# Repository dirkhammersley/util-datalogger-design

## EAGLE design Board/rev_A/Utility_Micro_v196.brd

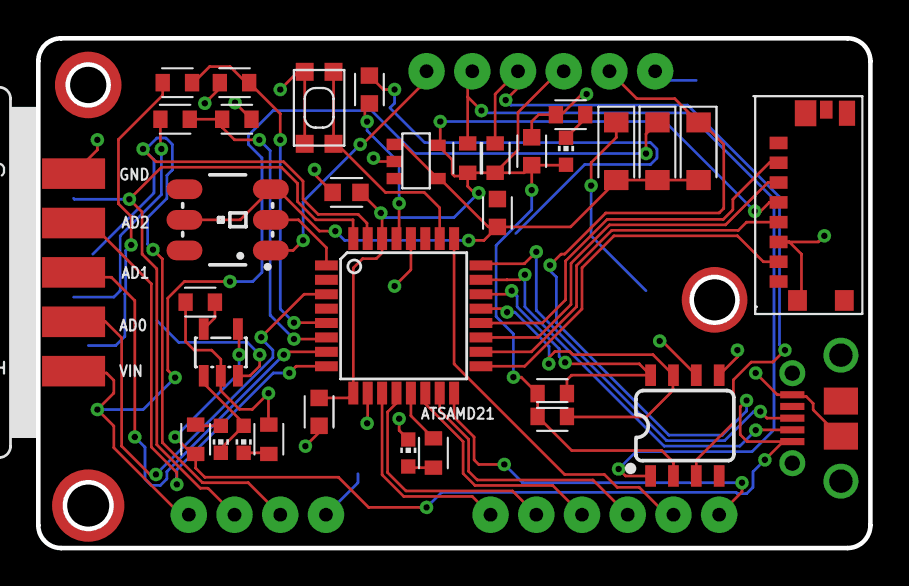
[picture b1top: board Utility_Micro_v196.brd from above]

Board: 2 copper layers, 46.2 x 28.3 mm, 38 parts (1 on the bottom side), 43 nets.

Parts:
ATSAMD21: ATSAMD21TQFP; TQFP32-08
C1, C2: 100nF; CAPC1608X85
C5, C8: C_CHIP-0603(1608-METRIC); CAPC1608X85
C7: 1uF; CAPC1608X85
D1, D2, D3: SCHOTTKY_MBR0520LT1GDO-219-AB(SOD123F); SODFL3718X115
IC1: MCP73831/OT; SOT23-5L
LED1, LED2, LED3, LED8: CHIP-LED0603
LIR_2450: LIR2450H; BC-2005
R1, R6, R7: 470; RESC1608X60
R2, R4: 100; RESC1608X60
R3: 2.2k; RESC1608X60
R5: 12k; RESC1608X60
R8, R9, R12, R13: 10k; RESC1608X60
R10, R11: 1k; RESC1608X60
RTC1: DS3231M; SO08
SW1: SPST_TACT-KMR2; KMR2
U1: WS2812; LED-TRICOLOR-5050-IC
U$2: MOLEX_MICRO_USB
U$3: AP2112; SOT-25
U$4, U$5: TP_SMALL_6_DEVICE; TP_SMALL_6
U$6: SMALL_MICRO_SD; MICRO_SD_SMALL
U$10: TP_SMALL_4_DEVICE; TP_SMALL_4
X2: F09D

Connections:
3V3: ATSAMD21.9, ATSAMD21.30, C1.2, C2.2, C5.1, LED8.A, R8.2, R9.2, R12.2, R13.2, RTC1.2, U$3.P$5, U$4.P$3, U$6.VDD
48_V: R3.2, X2.6
DMIN: ATSAMD21.23, U$2.DMIN
DPLU: ATSAMD21.24, U$2.DPLUS
GND: ATSAMD21.10, ATSAMD21.28, C1.1, C2.1, C5.2, C7.1, C8.2, IC1.2, LED3.C, LIR_2450.P$3, R2.1, R4.1, R5.2, R7.1, R10.1, RTC1.5, SW1.2, SW1.4, U1.6, U$2.CASE_GND, U$2.GND, U$3.P$2, U$4.P$1, U$10.P$1, X2.5
GPIO1: ATSAMD21.3, X2.2
GPIO2: ATSAMD21.7, X2.3
GPIO3: ATSAMD21.8, X2.4
GPIO4: ATSAMD21.11, U$5.P$1
GPIO5: ATSAMD21.12, U$5.P$2
GPIO6: ATSAMD21.14, U$5.P$3
GPIO7: ATSAMD21.15, U$5.P$4
GPIO8: ATSAMD21.25, U$5.P$5
GPIO9: ATSAMD21.16, U$5.P$6
MISO: ATSAMD21.17, U$6.DAT0
MOSI: ATSAMD21.19, U$6.CMD
unnamed: LED3.A, R11.1
unnamed: U$6.GND1, U$6.GND2, U$6.GND3, U$6.GND4, U$6.GND5, U$6.VSS
unnamed: ATSAMD21.13, R11.2
unnamed: ATSAMD21.29, C7.2
unnamed: R1.2, X2.7
unnamed: IC1.5, R5.1
unnamed: LED1.A, R6.2
unnamed: LED2.C, R7.2
unnamed: IC1.1, LED1.C, LED2.A
unnamed: LED8.C, R10.2
REG_VIN: C8.1, D1.2, D2.2, D3.2, U1.3, U1.5, U$3.P$1, U$3.P$4
RST: ATSAMD21.26, SW1.1, SW1.3
RTC_32KHZ: R12.1, RTC1.1, U$4.P$5
RTC_SCL: ATSAMD21.22, R8.1, RTC1.8
RTC_SDA: ATSAMD21.21, R9.1, RTC1.7
RTC_SQW: R13.1, RTC1.3, U$4.P$4
SCLK: ATSAMD21.18, U$6.SCLK
SEL: ATSAMD21.20, U$6.CS
SWDC: ATSAMD21.31, U$10.P$2, X2.8
SWDD: ATSAMD21.32, U$10.P$3, X2.9
UL1: ATSAMD21.1, U1.2
ULED_OUT: U1.1, U$4.P$6
VBAT: D2.1, IC1.3, LIR_2450.P$1, LIR_2450.P$2, RTC1.6
VBUS: D3.1, IC1.4, R6.1, U$2.VBUS, U$4.P$2
VCC: D1.1, U$10.P$4, X2.1
V_12: ATSAMD21.6, R1.1, R2.2
V_48: ATSAMD21.5, R3.1, R4.2

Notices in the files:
parts and their libraries:
SparkFun-Clocks: Licensing: Creative Commons ShareAlike 4.0 International - https://creativecommons.org/licenses/by-sa/4.0
